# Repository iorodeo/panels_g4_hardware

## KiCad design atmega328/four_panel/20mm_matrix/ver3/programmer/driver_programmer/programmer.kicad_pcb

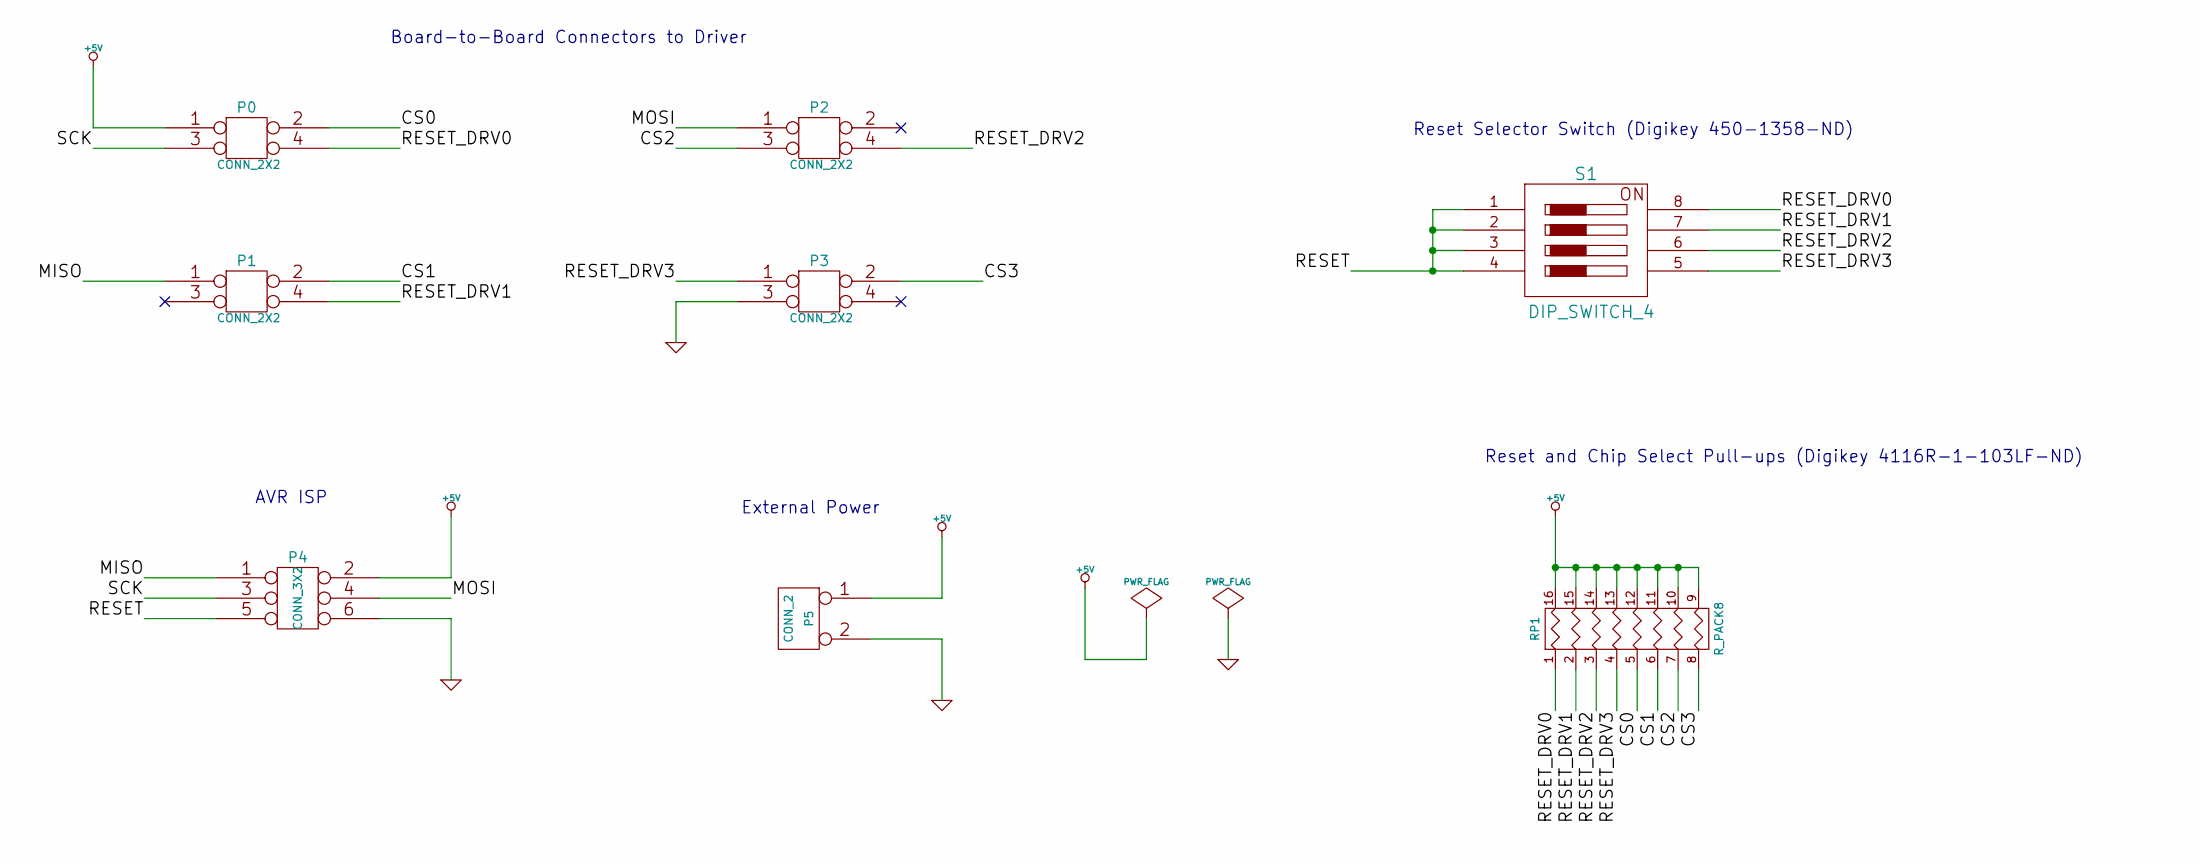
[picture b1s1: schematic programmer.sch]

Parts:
P0, P1, P2, P3: CONN_2X2
P4: CONN_3X2
P5: CONN_2
RP1: R_PACK8
S1: DIP_SWITCH_4

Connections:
+5V: P0.1, P4.2, P5.1, RP1.9 (R8), RP1.10 (R7), RP1.11 (R6), RP1.12 (R5), RP1.13 (R4), RP1.14 (R3), RP1.15 (R2), RP1.16 (R1)
/CS0: P0.2, RP1.5
/CS1: P1.2, RP1.6
/CS2: P2.3, RP1.7
/CS3: P3.2, RP1.8
/MISO: P1.1, P4.1
/MOSI: P2.1, P4.4
/RESET: P4.5, S1.1, S1.2, S1.3, S1.4
/RESET_DRV0: P0.4, RP1.1, S1.8
/RESET_DRV1: P1.4, RP1.2, S1.7
/RESET_DRV2: P2.4, RP1.3, S1.6
/RESET_DRV3: P3.1, RP1.4, S1.5
/SCK: P0.3, P4.3
GND: P3.3, P4.6, P5.2 (PM)

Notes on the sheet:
AVR ISP
External Power
Board-to-Board Connectors to Driver
Reset and Chip Select Pull-ups (Digikey 4116R-1-103LF-ND)
Reset Selector Switch (Digikey 450-1358-ND)

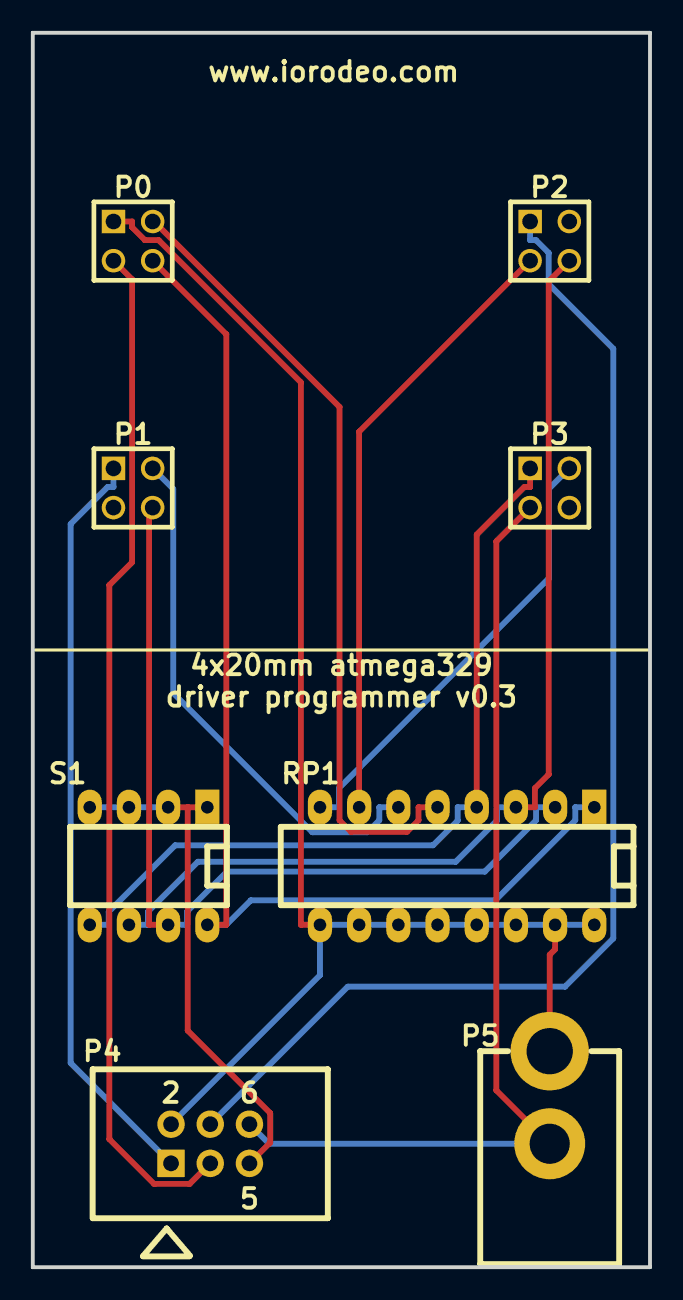
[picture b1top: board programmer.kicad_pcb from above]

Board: 2 copper layers, 40.0 x 80.0 mm, 8 parts (0 on the bottom side), 14 nets.

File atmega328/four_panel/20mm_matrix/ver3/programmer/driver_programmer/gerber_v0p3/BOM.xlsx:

Item # | Qty | Reference | Description | PN | Vendor |  | unit price |  | price
1 | 4 | P0-P3 | 2x2 male header, 0.1” pitch | 952-2119-ND | Digikey |  | 0.24 |  | 0.96
2 | 1 | P4 | 3x2 male header, shourded, 0.1” pitch | 854 | Pololu |  | 0.97 |  | 0.97
3 | 1 | P5 | DC Jack, 2.1mm, 2 pin | 137673 | Jameco |  | 0.45 |  | 0.45
4 | 1 | RP1 | Resistor array, 8 resistor, 10k | 4116R-1-103LF-ND | Digikey |  | 0.76 |  | 0.76
5 | 1 | S1 | Dip switch, 4 pos | 450-1358-ND | Digikey |  | 0.74 |  | 0.74
Extra
1 | 2 | P2 | Mating IDC socket for 3x2 shrouded header | 855 | Pololu |  | 0.97 |  | 1.94
 |  |  |  |  |  |  |  |  | 5.82

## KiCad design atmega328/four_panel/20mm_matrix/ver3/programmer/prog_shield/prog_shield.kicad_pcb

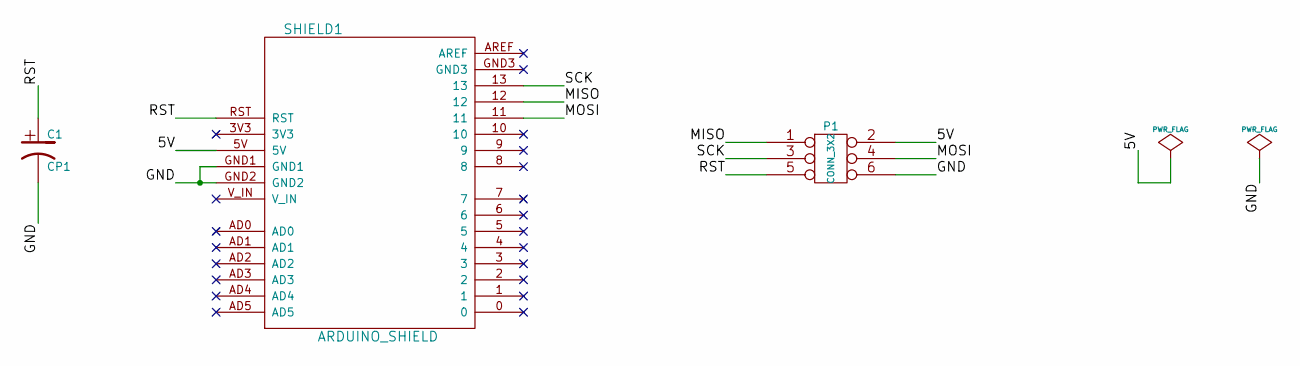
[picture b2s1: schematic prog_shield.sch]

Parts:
C1: CP1
P1: CONN_3X2
SHIELD1: ARDUINO_SHIELD

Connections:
/5V: P1.2, SHIELD1.5V
/GND: C1.2, P1.6, SHIELD1.GND1, SHIELD1.GND2
/MISO: P1.1, SHIELD1.12
/MOSI: P1.4, SHIELD1.11
/RST: C1.1, P1.5, SHIELD1.RST
/SCK: P1.3, SHIELD1.13

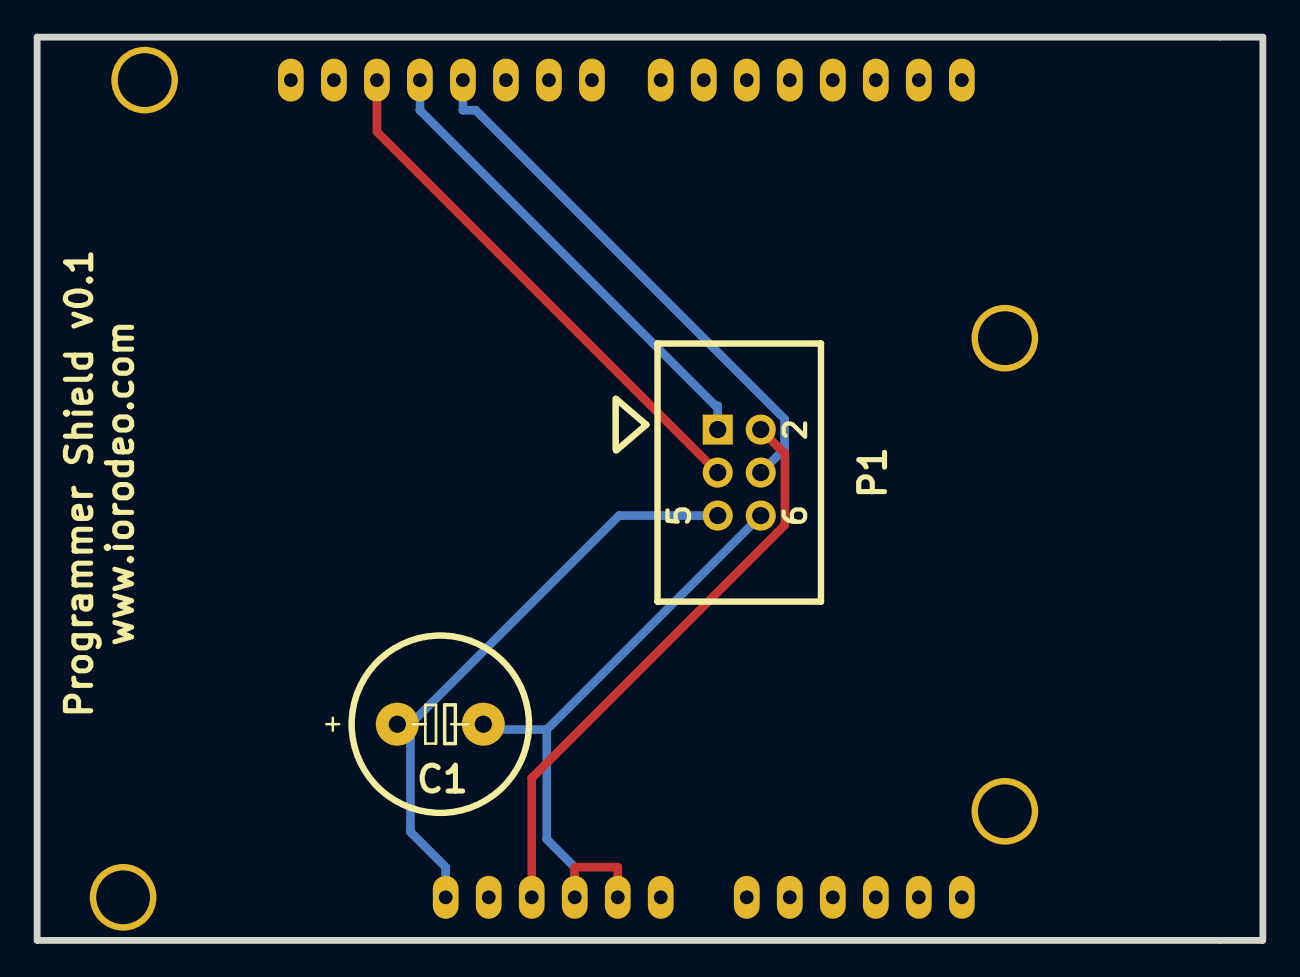
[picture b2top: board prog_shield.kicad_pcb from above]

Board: 2 copper layers, 72.4 x 53.3 mm, 3 parts (0 on the bottom side), 6 nets.

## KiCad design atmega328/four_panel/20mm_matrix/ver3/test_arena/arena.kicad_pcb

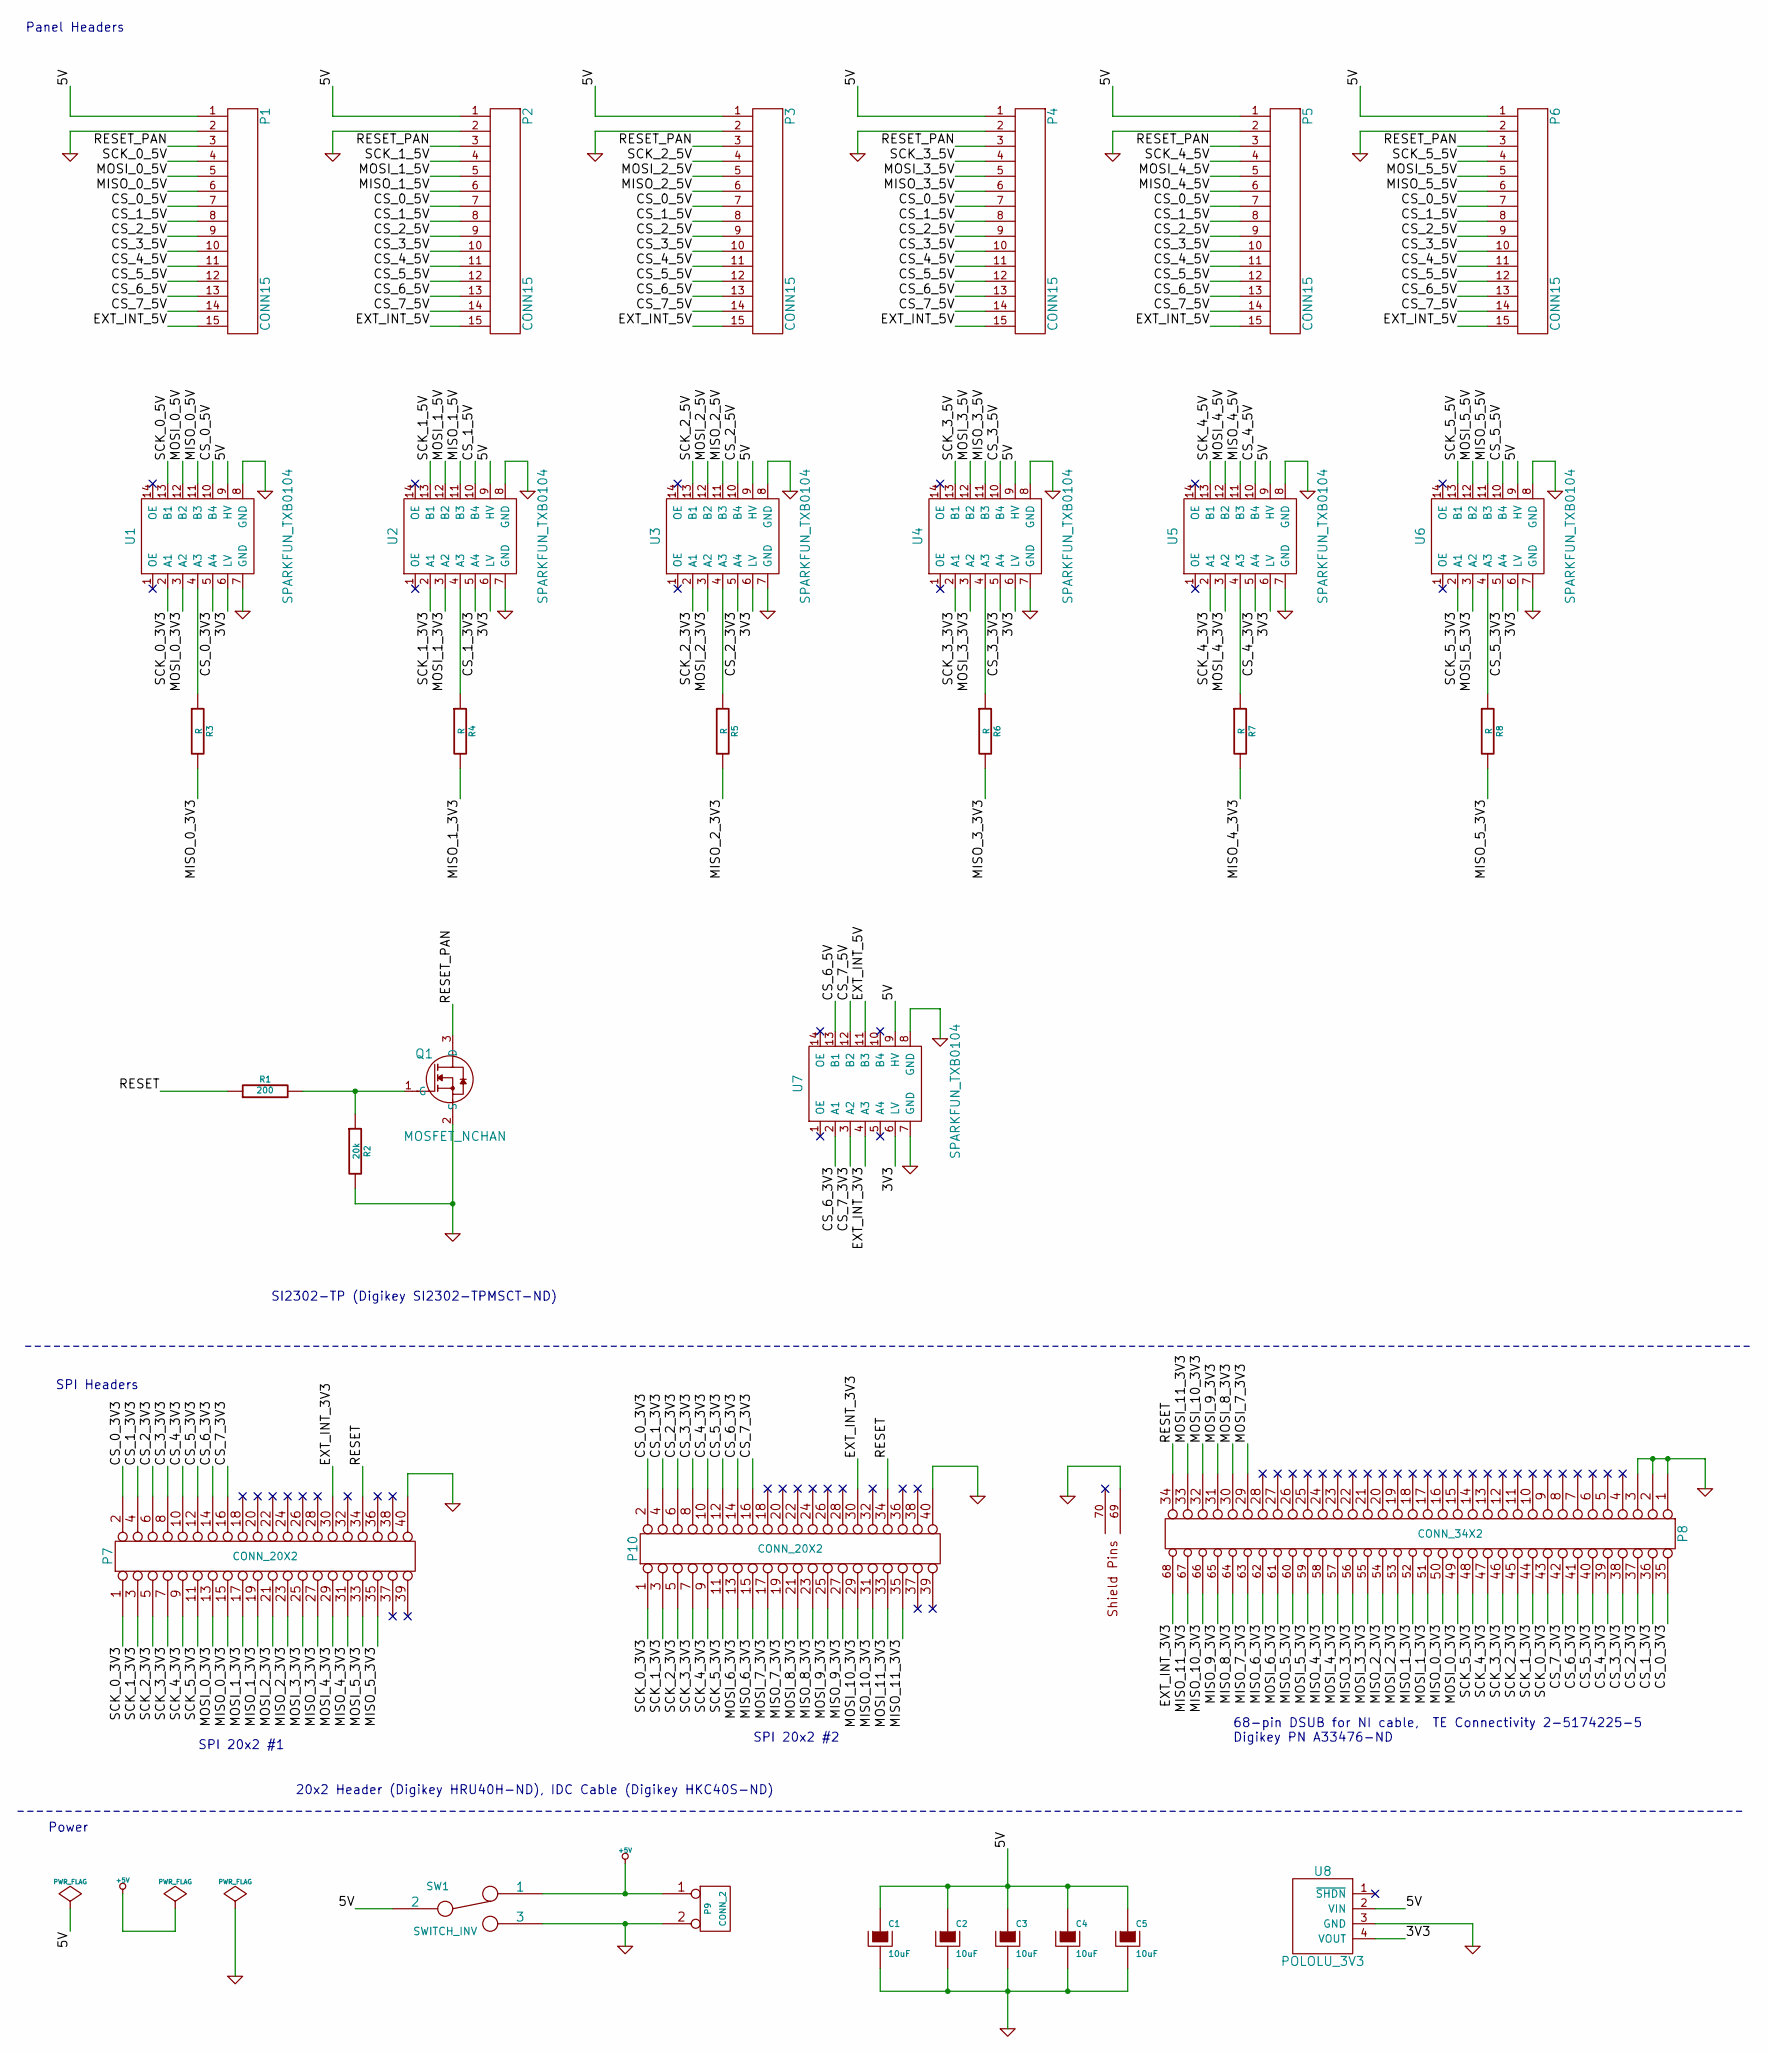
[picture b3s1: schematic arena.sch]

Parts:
C1, C2, C3, C4, C5: 10uF
P1, P2, P3, P4, P5, P6: CONN15
P7, P10: CONN_20X2
P8: CONN_34X2
P9: CONN_2
Q1: MOSFET_NCHAN
R1: 200
R2: 20k
R3, R4, R5, R6, R7, R8: R
SW1: SWITCH_INV
U1, U2, U3, U4, U5, U6, U7: SPARKFUN_TXB0104
U8: POLOLU_3V3

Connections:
+5V: P9.1, SW1.1
/3V3: U1.6 (LV), U2.6 (LV), U3.6 (LV), U4.6 (LV), U5.6 (LV), U6.6 (LV), U7.6 (LV), U8.4 (VOUT)
/5V: C1.1, C2.1, C3.1, C4.1, C5.1, P1.1, P2.1, P3.1, P4.1, P5.1, P6.1, SW1.2, U1.9 (HV), U2.9 (HV), U3.9 (HV), U4.9 (HV), U5.9 (HV), U6.9 (HV), U7.9 (HV), U8.2 (VIN)
/CS_0_3V3: P7.2, P8.35, P10.2, U1.5 (A4)
/CS_0_5V: P1.7, P2.7, P3.7, P4.7, P5.7, P6.7, U1.10 (B4)
/CS_1_3V3: P7.4, P8.36, P10.4, U2.5 (A4)
/CS_1_5V: P1.8, P2.8, P3.8, P4.8, P5.8, P6.8, U2.10 (B4)
/CS_2_3V3: P7.6, P8.37, P10.6, U3.5 (A4)
/CS_2_5V: P1.9, P2.9, P3.9, P4.9, P5.9, P6.9, U3.10 (B4)
/CS_3_3V3: P7.8, P8.38, P10.8, U4.5 (A4)
/CS_3_5V: P1.10, P2.10, P3.10, P4.10, P5.10, P6.10, U4.10 (B4)
/CS_4_3V3: P7.10, P8.39, P10.10, U5.5 (A4)
/CS_4_5V: P1.11, P2.11, P3.11, P4.11, P5.11, P6.11, U5.10 (B4)
/CS_5_3V3: P7.12, P8.40, P10.12, U6.5 (A4)
/CS_5_5V: P1.12, P2.12, P3.12, P4.12, P5.12, P6.12, U6.10 (B4)
/CS_6_3V3: P7.14, P8.41, P10.14, U7.2 (A1)
/CS_6_5V: P1.13, P2.13, P3.13, P4.13, P5.13, P6.13, U7.13 (B1)
/CS_7_3V3: P7.16, P8.42, P10.16, U7.3 (A2)
/CS_7_5V: P1.14, P2.14, P3.14, P4.14, P5.14, P6.14, U7.12 (B2)
/EXT_INT_3V3: P7.30, P8.68, P10.30, U7.4 (A3)
/EXT_INT_5V: P1.15, P2.15, P3.15, P4.15, P5.15, P6.15, U7.11 (B3)
/MISO_0_3V3: P7.15, P8.50, R3.2
/MISO_0_5V: P1.6, U1.11 (B3)
/MISO_1_3V3: P7.19, P8.52, R4.2
/MISO_1_5V: P2.6, U2.11 (B3)
/MISO_2_3V3: P7.23, P8.54, R5.2
/MISO_2_5V: P3.6, U3.11 (B3)
/MISO_3_3V3: P7.27, P8.56, R6.2
/MISO_3_5V: P4.6, U4.11 (B3)
/MISO_4_3V3: P7.31, P8.58, R7.2
/MISO_4_5V: P5.6, U5.11 (B3)
/MISO_5_3V3: P7.35, P8.60, R8.2
/MISO_5_5V: P6.6, U6.11 (B3)
/MISO_6_3V3: P8.62, P10.15
/MISO_7_3V3: P8.63, P10.19
/MISO_8_3V3: P8.64, P10.23
/MISO_9_3V3: P8.65, P10.27
/MISO_10_3V3: P8.66, P10.31
/MISO_11_3V3: P8.67, P10.35
/MOSI_0_3V3: P7.13, P8.49, U1.3 (A2)
/MOSI_0_5V: P1.5, U1.12 (B2)
/MOSI_1_3V3: P7.17, P8.51, U2.3 (A2)
/MOSI_1_5V: P2.5, U2.12 (B2)
/MOSI_2_3V3: P7.21, P8.53, U3.3 (A2)
/MOSI_2_5V: P3.5, U3.12 (B2)
/MOSI_3_3V3: P7.25, P8.55, U4.3 (A2)
/MOSI_3_5V: P4.5, U4.12 (B2)
/MOSI_4_3V3: P7.29, P8.57, U5.3 (A2)
/MOSI_4_5V: P5.5, U5.12 (B2)
/MOSI_5_3V3: P7.33, P8.59, U6.3 (A2)
/MOSI_5_5V: P6.5, U6.12 (B2)
/MOSI_6_3V3: P8.61, P10.13
/MOSI_7_3V3: P8.29, P10.17
/MOSI_8_3V3: P8.30, P10.21
/MOSI_9_3V3: P8.31, P10.25
/MOSI_10_3V3: P8.32, P10.29
/MOSI_11_3V3: P8.33, P10.33
/RESET: P7.34, P8.34, P10.34, R1.1
/RESET_PAN: P1.3, P2.3, P3.3, P4.3, P5.3, P6.3, Q1.3 (D)
/SCK_0_3V3: P7.1, P8.43, P10.1, U1.2 (A1)
/SCK_0_5V: P1.4, U1.13 (B1)
/SCK_1_3V3: P7.3, P8.44, P10.3, U2.2 (A1)
/SCK_1_5V: P2.4, U2.13 (B1)
/SCK_2_3V3: P7.5, P8.45, P10.5, U3.2 (A1)
/SCK_2_5V: P3.4, U3.13 (B1)
/SCK_3_3V3: P7.7, P8.46, P10.7, U4.2 (A1)
/SCK_3_5V: P4.4, U4.13 (B1)
/SCK_4_3V3: P7.9, P8.47, P10.9, U5.2 (A1)
/SCK_4_5V: P5.4, U5.13 (B1)
/SCK_5_3V3: P7.11, P8.48, P10.11, U6.2 (A1)
/SCK_5_5V: P6.4, U6.13 (B1)
GND: C1.2, C2.2, C3.2, C4.2, C5.2, P1.2, P2.2, P3.2, P4.2, P5.2, P6.2, P7.40, P8.1, P8.2, P8.3, P8.69, P9.2 (PM), P10.40, Q1.2 (S), R2.2, SW1.3, U1.7 (GND), U1.8 (GND), U2.7 (GND), U2.8 (GND), U3.7 (GND), U3.8 (GND), U4.7 (GND), U4.8 (GND), U5.7 (GND), U5.8 (GND), U6.7 (GND), U6.8 (GND), U7.7 (GND), U7.8 (GND), U8.3 (GND)
unnamed: Q1.1 (G), R1.2, R2.1
unnamed: R7.1, U5.4 (A3)
unnamed: R4.1, U2.4 (A3)
unnamed: R5.1, U3.4 (A3)
unnamed: R6.1, U4.4 (A3)
unnamed: R8.1, U6.4 (A3)
unnamed: R3.1, U1.4 (A3)

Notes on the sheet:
Power
Panel Headers
SPI Headers
20x2 Header (Digikey HRU40H-ND), IDC Cable (Digikey HKC40S-ND)
68-pin DSUB for NI cable, TE Connectivity 2-5174225-5 Digikey PN A33476-ND
SI2302-TP (Digikey SI2302-TPMSCT-ND)
SPI 20x2 #1
SPI 20x2 #2

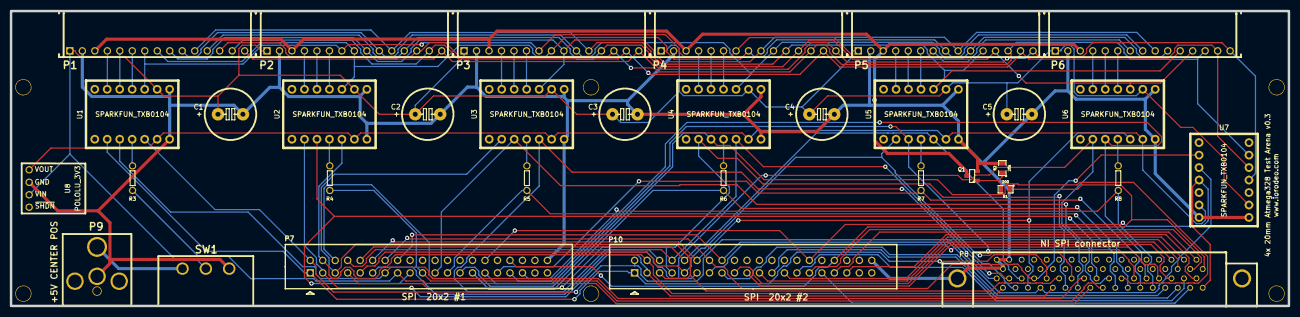
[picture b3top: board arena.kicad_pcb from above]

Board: 2 copper layers, 260.0 x 60.0 mm, 39 parts (0 on the bottom side), 79 nets.

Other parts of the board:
M1, M2, M3, M4, M5, M6: VAL**; MOUNT_HOLE_4_40
